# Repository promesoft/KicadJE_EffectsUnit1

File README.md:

# KicadJE_EffectsUnit1
JE-EU1 - PT2399 based reverb - distortion units
Eurorack form factor

# MK1 Design
## Status - operational
# Status - Secondary tests
## Initial 
| Stage  | Detail | Status |
| ------------- | ------------- | ------------- |
| create material  | sch/pcb | produced Rev A  |
| | gerber | Produced |
| production  | ordered  | YES |
|  | produced | YES |
|  | delivered | YES |
## Preliminary validation
| Test  | Detail | Status |
| ------------- | ------------- | ------------- |
| Initial Inspection |  | OK |
| Initial Technical Test | PT2399 | OK - See Errata |
| Initial Technical Test | Counter  | OK |
| Initial Technical Test | Bitcrunch |  |
| Initial Product Test | PT2399 | OK |
| Initial Product Test | Counter | OK |
| Initial Product Test | Bitcrunch  | OK - LFO w Distortion |
| Initial Power Consumption | PT2399 | 40-60mA ! +12v depending on VCO circuit |
| Initial Power Consumption | Counter | 20mA +12v  |
| Initial Power Consumption | Bitcrunch | +12v +5v -12v |
| Initial Power Consumption | LFO | +12v +5v -12v |

## Secondary validation
| Test  | Detail | Status |
| ------------- | ------------- |------------- |
| Product Test | PT2399 | ok after mod |
| Product Test | Counter | OK |
| Product Test | LFO Distortion | OK - dist too much |
| Product Test | Bitcrush Distortion |  |
| Quality | LFO | good - distortion is questionable effect |
| Quality | Bitcrush |  |
| Quality | Counter | Good - needs input prot |
| Quality | PT2399 | ongoing |
| Long Term Product Test | PT2399 | Modded version installed in rack |
| Long Term Product Test | Counter | installed in rack |
| Long Term Product Test | Bitcrush |  |
| Long Term Product Test | LFO | installed in rack |

## Software 
| Test  | Detail | Status |
| ------------- | ------------- |------------- |
| Initial SW | copy from MK1 and adjusted | OK! |
| Bitcrush | UI | |
| Bitcrush | Crush function | |
| LFO Control | UI | Individual speed and waveform impl |
| LFO Control | Function | Individual LFO implemented |
| LFO Control | Input | 3x Trigger done |

## Errata
### ERRATA - PT2399
 * 78L05 inv pinout
 * MMBT2222 wrong pinout - workaround flip and turn
 * Delay time pot reversed
 * PT2399 occational latchup with modification
 * SW101 and S105W are wired wrong to enable Dist on/off
### ERRATA - Counter
### ERRATA - Bitcrunch
 * SW 101 and SW105 should change footprint (too small for MT202)
 * D110 and D111 is 0805 and cannot be fitted with SOD123
## Issues and Notes
### Issues and Notes - PT2399
 * Replace 20k across Q203 w Yellow LED
 * Replace 120k R214 with 47k
 * Move C222 across RV202 - move D2015 across R214 and remove Q202+R213
 * Consider Vactrol of RV202 and RV201
 * Consider +5V supply...
### Issues and Notes - Counter
 * Replace 100uF C310 with 10-22uF (consider a switch for next rev)
 * Reset/Clk in Trigger not 5V tolerant
 * Add I/O protection

### Issues and Notes - Bit Crunch
LFO only values:
 * 11k = 10k
 * 22k = 10k
 * 33k = 10k
 * 44k = 10k
 * 11n = 100n
 * 22n = 100n
 * 33n = 100n
 * 44n = 100n
 * D118 - D117 remove
 * Optional D111 - D110
Dist/Bitcrush values has been added to the sch
 * Move LED D114 closer to Out9

### Workarounds

## Base Construction 
The idea is to have 3 different units.
Practically it may be required to fit the bitcrusher and the distortion in one unit.
### Distortion base board with Arduino Bitcrusher
 - 16pin Europower connector

### PT2399 base board 
 - 10pin Europower connector
 - BC547 or BC337 NPN and Zener 7v5 regulator followed by 78L05 regulator
 - PT2399 echo circuit with anti lockup circuit for pin 6
 - 
### Binary counter and clock
 - 10pin Europower connector
 - Build around a CD4017 counter chip (SOP-14)

## Vital Components
 - Arduino Nano
 - PT2399
 - CD4017
 - NE555
 - Mini Jacks (PJ-321) 
 - ALPS RV09 potentiometer
 - TL072 or similar dual op amp
 - Diode clipping (silicium signal diodes, LED, power, shottkey, germanium
 
### Mechanical

The construction is inspired from
-----------------------------------------------------
 - https://www.electronics-tutorials.ws/waveforms/555_oscillator.html (Counter clock)
 - https://www.electrosmash.com/pt2399-analysis (PT2399 Reverb)
 - http://sim.okawa-denshi.jp/en/OPttool.php (Filter calc for MFB filter)
 - http://sim.okawa-denshi.jp/en/OPseikiLowkeisan.htm (Filter calc for Sallen Key filter (Out9 and Out10))

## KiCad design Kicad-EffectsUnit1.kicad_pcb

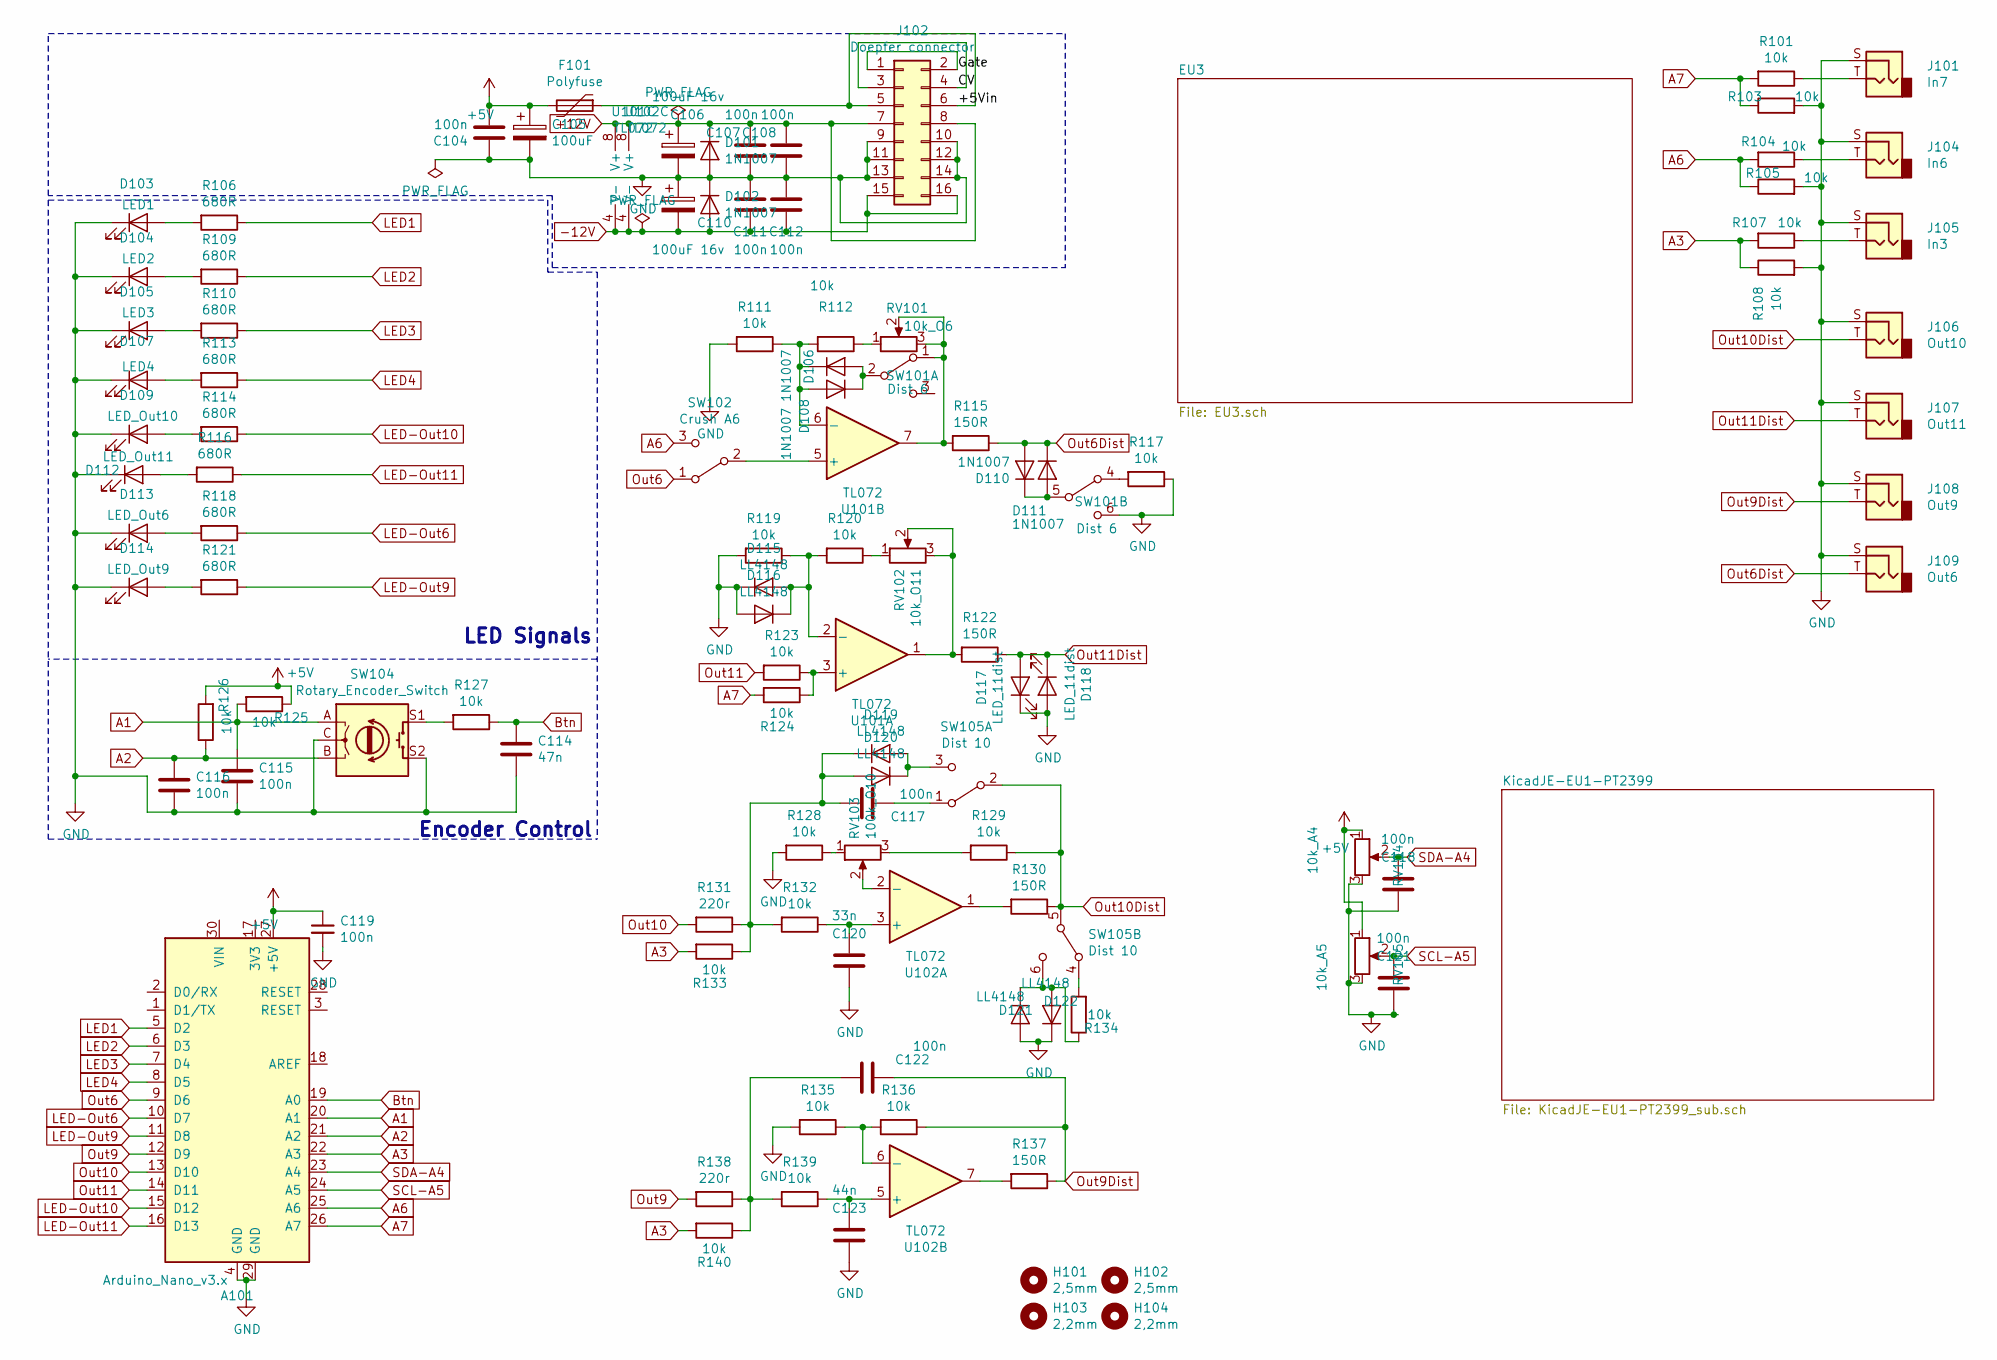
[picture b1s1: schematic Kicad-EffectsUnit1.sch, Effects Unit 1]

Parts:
A101: Arduino_Nano_v3.x; Arduino_Nano
C104, C107, C108, C111, C112, C115, C116, C117, C118, C119, C121, C122: 100n; C_0805_2012Metric_Pad1.15x1.40mm_HandSolder
C105: 100uF; CP_Radial_D5.0mm_P2.50mm
C106, C110: 100uF 16v; CP_Radial_D5.0mm_P2.50mm
C114: 47n; C_0805_2012Metric_Pad1.15x1.40mm_HandSolder
C120: 33n; C_0805_2012Metric_Pad1.15x1.40mm_HandSolder
C123: 44n; C_0805_2012Metric_Pad1.15x1.40mm_HandSolder
D101, D102, D106, D108: 1N1007; D_SOD-123
D103: LED1; LED_D3.0mm
D104: LED2; LED_D3.0mm
D105: LED3; LED_D3.0mm
D107: LED4; LED_D3.0mm
D109: LED_Out10; LED_D3.0mm
D110, D111: 1N1007; D_0805_2012Metric_Pad1.15x1.40mm_HandSolder
D112: LED_Out11; LED_D3.0mm
D113: LED_Out6; LED_D3.0mm
D114: LED_Out9; LED_D3.0mm
D115, D116, D119, D120, D121, D122: LL4148; D_MiniMELF
D117: LED_11dist; LED_0805_2012Metric_Pad1.15x1.40mm_HandSolder
D118: LED_11dist; D_0805_2012Metric_Pad1.15x1.40mm_HandSolder
F101: Polyfuse; Fuse_1206_3216Metric_Pad1.42x1.75mm_HandSolder
H101, H102: 2,5mm; MountingHole_2.5mm_Pad_Via
H103: 2,2mm; MountingHole_2.5mm_Pad_Via
H104: 2,2mm; MountingHole_2.2mm_M2_Pad_Via
J101: In7; PJ301SM
J102: Doepfer connector; PinSocket_2x08_P2.54mm_Vertical
J104: In6; PJ301SM
J105: In3; PJ301SM
J106: Out10; PJ301SM
J107: Out11; PJ301SM
J108: Out9; PJ301SM
J109: Out6; PJ301SM
R101, R103, R104, R105, R107, R108, R111, R112, R117, R119, R120, R123, R124, R125, R126, R127, R128, R129, R132, R133, R134, R135, R136, R139, R140: 10k; R_0805_2012Metric_Pad1.15x1.40mm_HandSolder
R106, R109, R110, R113, R114, R116, R118, R121: 680R; R_0805_2012Metric_Pad1.15x1.40mm_HandSolder
R115, R122, R130, R137: 150R; R_0805_2012Metric_Pad1.15x1.40mm_HandSolder
R131, R138: 220r; R_0805_2012Metric_Pad1.15x1.40mm_HandSolder
RV101: 10k_O6; Potentiometer_China_RK09_Single_Vertical_AJ
RV102: 10k_O11; Potentiometer_China_RK09_Single_Vertical_AJ
RV103: 100k_O10; Potentiometer_China_RK09_Single_Vertical_AJ
RV104: 10k_A4; Potentiometer_China_RK09_Single_Vertical_AJ
RV105: 10k_A5; Potentiometer_China_RK09_Single_Vertical_AJ
SW101: Dist 6; SPDTx2
SW102: Crush A6; SP1MS1
SW104: Rotary_Encoder_Switch; RotaryEncoder_Alps_EC11E-Switch_Vertical_H20mm
SW105: Dist 10; SPDTx2
U101, U102: TL072; AJ_SO-8_5.3x6.2mm_P1.27mm

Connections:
+5V: A101.27 (+5V), C104.2, C105.1, C119.1, F101.2, R125.1, R126.2, RV104.1, RV105.1
+12V: C106.1, C107.2, C108.2, D101.1 (K), J102.7, J102.8, U101.8 (V+), U102.8 (V+)
-12V: C110.2, C111.1, C112.1, D102.2 (A), J102.15, J102.16, U101.4 (V-), U102.4 (V-)
/+5Vin: F101.1, J102.5, J102.6
/CV: J102.3, J102.4
/Gate: J102.1, J102.2
A1: A101.20 (A1), C115.1, R125.2, SW104.A
A2: A101.21 (A2), C116.1, R126.1, SW104.B
A3: A101.22 (A3), R107.2, R108.1, R133.2, R140.2
A6: A101.25 (A6), R104.2, R105.1, SW102.3 (C)
A7: A101.26 (A7), R101.2, R103.1, R124.2
Btn: A101.19 (A0), C114.1, R127.1
GND: A101.4 (GND), A101.29 (GND), C104.1, C105.2, C106.2, C107.1, C108.1, C110.1, C111.2, C112.2, C114.2, C115.2, C116.2, C118.2, C119.2, C120.2, C121.2, C123.2, D101.2 (A), D102.1 (K), D103.1 (K), D104.1 (K), D105.1 (K), D107.1 (K), D109.1 (K), D112.1 (K), D113.1 (K), D114.1 (K), D115.1 (K), D116.2 (A), D117.1 (K), D118.2 (A), D121.2 (A), D122.1 (K), J101.S, J102.9, J102.10, J102.11, J102.12, J102.13, J102.14, J104.S, J105.S, J106.S, J107.S, J108.S, J109.S, R103.2, R105.2, R108.2, R111.2, R117.1, R119.2, R128.2, R135.2, RV104.3, RV105.3, SW101.6 (C), SW104.C, SW104.S2; also elsewhere on the board
LED1: A101.5 (D2), R106.1
LED2: A101.6 (D3), R109.1
LED3: A101.7 (D4), R110.1
LED4: A101.8 (D5), R113.1
LED-Out6: A101.10 (D7), R118.1
LED-Out9: A101.11 (D8), R121.1
LED-Out10: A101.15 (D12), R114.1
LED-Out11: A101.16 (D13), R116.1
unnamed: C117.1, SW105.1 (A)
unnamed: C117.2, D119.1 (K), D120.2 (A), R131.1, R132.2, R133.1
unnamed: C120.1, R132.1, U102.3 (+)
unnamed: C122.2, R138.1, R139.2, R140.1
unnamed: C123.1, R139.1, U102.5 (+)
unnamed: D103.2 (A), R106.2
unnamed: D104.2 (A), R109.2
unnamed: D105.2 (A), R110.2
unnamed: D106.1 (K), D108.2 (A), R111.1, R112.2, U101.6 (-)
unnamed: D106.2 (A), D108.1 (K), SW101.2 (B)
unnamed: D107.2 (A), R113.2
unnamed: D109.2 (A), R114.2
unnamed: D110.1 (K), D111.2 (A), SW101.5 (B)
unnamed: D112.2 (A), R116.2
unnamed: D113.2 (A), R118.2
unnamed: D114.2 (A), R121.2
unnamed: D115.2 (A), D116.1 (K), R119.1, R120.2, U101.2 (-)
unnamed: D119.2 (A), D120.1 (K), SW105.3 (C)
unnamed: D121.1 (K), D122.2 (A), R134.1, SW105.6 (C)
unnamed: J101.T, R101.1
unnamed: J104.T, R104.1
unnamed: J105.T, R107.1
unnamed: R112.1, RV101.1
unnamed: R115.2, RV101.2, RV101.3, SW101.1 (A), U101.7
unnamed: R117.2, SW101.4 (A)
unnamed: R120.1, RV102.1
unnamed: R122.2, RV102.2, RV102.3, U101.1
unnamed: R123.1, R124.1, U101.3 (+)
unnamed: R127.2, SW104.S1
unnamed: R128.1, RV103.1
unnamed: R129.2, RV103.3
unnamed: R130.2, U102.1
unnamed: R134.2, SW105.4 (A)
unnamed: R135.1, R136.2, U102.6 (-)
unnamed: R137.2, U102.7
unnamed: RV103.2, U102.2 (-)
unnamed: SW102.2 (B), U101.5 (+)
Out6: A101.9 (D6), SW102.1 (A); also elsewhere on the board
Out6Dist: D110.2 (A), D111.1 (K), J109.T, R115.1
Out9: A101.12 (D9), R138.2; also elsewhere on the board
Out9Dist: C122.1, J108.T, R136.1, R137.1
Out10: A101.13 (D10), R131.2
Out10Dist: J106.T, R129.1, R130.1, SW105.2 (B), SW105.5 (B)
Out11: A101.14 (D11), R123.2
Out11Dist: D117.2 (A), D118.1 (K), J107.T, R122.1
SCL-A5: A101.24 (A5), C121.1, RV105.2
SDA-A4: A101.23 (A4), C118.1, RV104.2

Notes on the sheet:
LED Signals
Encoder Control

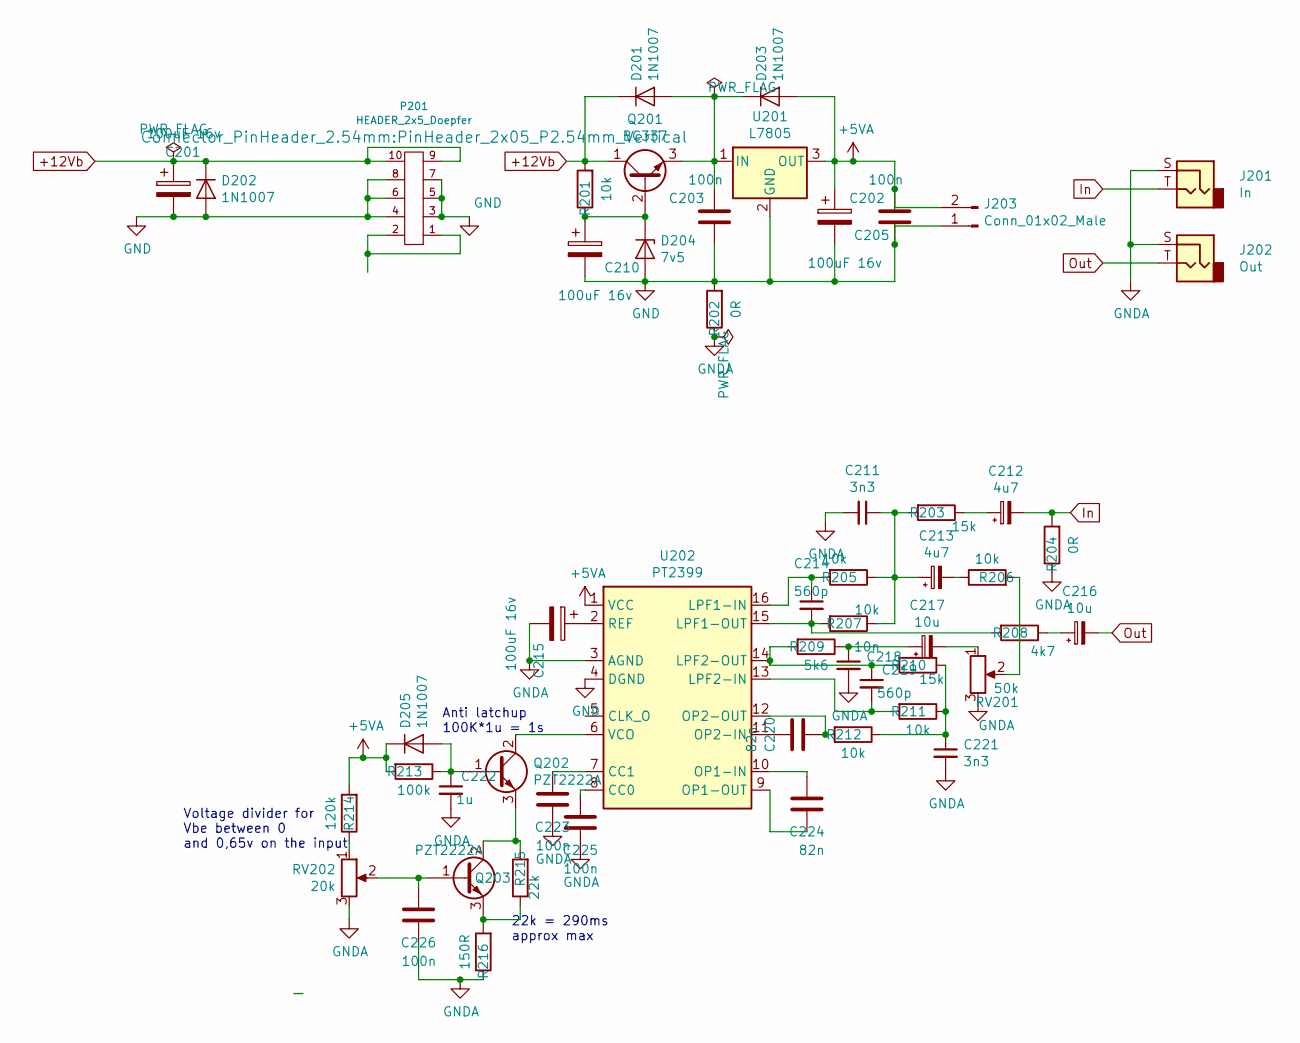
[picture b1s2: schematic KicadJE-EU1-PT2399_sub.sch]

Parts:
C201, C205, C210, C215: 100uF 16v; CP_Radial_D5.0mm_P2.50mm
C202, C203, C223, C225, C226: 100n; C_0805_2012Metric_Pad1.15x1.40mm_HandSolder
C211, C221: 3n3; C_0805_2012Metric_Pad1.15x1.40mm_HandSolder
C212, C213: 4u7; C_0805_2012Metric_Pad1.15x1.40mm_HandSolder
C214, C219: 560p; C_0805_2012Metric_Pad1.15x1.40mm_HandSolder
C216, C217: 10u; C_0805_2012Metric_Pad1.15x1.40mm_HandSolder
C218: 10n; C_0805_2012Metric_Pad1.15x1.40mm_HandSolder
C220, C224: 82n; C_0805_2012Metric_Pad1.15x1.40mm_HandSolder
C222: 1u; C_0805_2012Metric_Pad1.15x1.40mm_HandSolder
D201, D202, D203, D205: 1N1007; D_SOD-123
D204: 7v5; D_MiniMELF
J201: In; PJ301SM
J202: Out; PJ301SM
J203: Conn_01x02_Male; PinHeader_1x02_P2.54mm_Vertical
P201: HEADER_2x5_Doepfer; PinHeader_2x05_P2.54mm_Vertical
Q201: BC337; TO-92_Inline
Q202, Q203: PZT2222A; SOT-23
R201, R205, R206, R207, R211, R212: 10k; R_0805_2012Metric_Pad1.15x1.40mm_HandSolder
R202, R204: 0R; R_0805_2012Metric_Pad1.15x1.40mm_HandSolder
R203, R210: 15k; R_0805_2012Metric_Pad1.15x1.40mm_HandSolder
R208: 4k7; R_0805_2012Metric_Pad1.15x1.40mm_HandSolder
R209: 5k6; R_0805_2012Metric_Pad1.15x1.40mm_HandSolder
R213: 100k; R_0805_2012Metric_Pad1.15x1.40mm_HandSolder
R214: 120k; R_0805_2012Metric_Pad1.15x1.40mm_HandSolder
R215: 22k; R_0805_2012Metric_Pad1.15x1.40mm_HandSolder
R216: 150R; R_0805_2012Metric_Pad1.15x1.40mm_HandSolder
RV201: 50k; Potentiometer_China_RK09_Single_Vertical_AJ
RV202: 20k; Potentiometer_China_RK09_Single_Vertical_AJ
U201: L7805; TO-92
U202: PT2399; DIP-16_W7.62mm

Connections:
+5VA: C202.2, C205.1, D203.2 (A), D205.1 (K), J203.2, R213.2, R214.2, U201.3 (OUT), U202.1 (VCC)
+12Vb: C201.1, D201.1 (K), D202.1 (K), P201.9 (+12), P201.10 (+12), Q201.1 (C), R201.2
GND: C201.2, C202.1, C203.1, C205.2, C210.2, D202.2 (A), D204.2 (A), J203.1, P201.3 (GND), P201.4 (GND), P201.5 (GND), P201.6 (GND), P201.7 (GND), P201.8 (GND), R202.2, U201.2 (GND), U202.4 (DGND); also elsewhere on the board
GNDA: C211.2, C215.2, C218.2, C221.2, C222.2, C223.1, C225.1, C226.1, J201.S, J202.S, R202.1, R204.1, R216.1, RV201.3, RV202.3, U202.3 (AGND)
In: C212.2, J201.T, R204.2
unnamed: C203.2, D201.2 (A), D203.1 (K), Q201.3 (E), U201.1 (IN)
unnamed: C210.1, D204.1 (K), Q201.2 (B), R201.1
unnamed: C211.1, C213.1, R203.2, R205.1, R207.1
unnamed: C212.1, R203.1
unnamed: C213.2, R206.1
unnamed: C214.1, R205.2, U202.16 (LPF1-IN)
unnamed: C214.2, R207.2, R208.2, U202.15 (LPF1-OUT)
unnamed: C215.1, U202.2 (REF)
unnamed: C216.1, R208.1
unnamed: C217.1, C218.1, R209.1
unnamed: C217.2, RV201.1
unnamed: C219.1, R209.2, R210.2, U202.14 (LPF2-OUT)
unnamed: C219.2, R211.2, U202.13 (LPF2-IN)
unnamed: C220.1, U202.11 (OP2-IN)
unnamed: C220.2, R212.2, U202.12 (OP2-OUT)
unnamed: C221.1, R210.1, R211.1, R212.1
unnamed: C222.1, D205.2 (A), Q202.1 (B), R213.1
unnamed: C223.2, U202.7 (CC1)
unnamed: C224.1, U202.9 (OP1-OUT)
unnamed: C224.2, U202.10 (OP1-IN)
unnamed: C225.2, U202.8 (CC0)
unnamed: C226.2, Q203.1 (B), RV202.2
unnamed: P201.1 (-12), P201.2 (-12)
unnamed: Q202.2 (C), U202.6 (VCO)
unnamed: Q202.3 (E), Q203.2 (C), R215.2
unnamed: Q203.3 (E), R215.1, R216.2
unnamed: R206.2, RV201.2
unnamed: R214.1, RV202.1
Out: C216.2, J202.T

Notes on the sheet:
Voltage divider for Vbe between 0 and 0,65v on the input
Anti latchup 100K*1u = 1s
22k = 290ms approx max

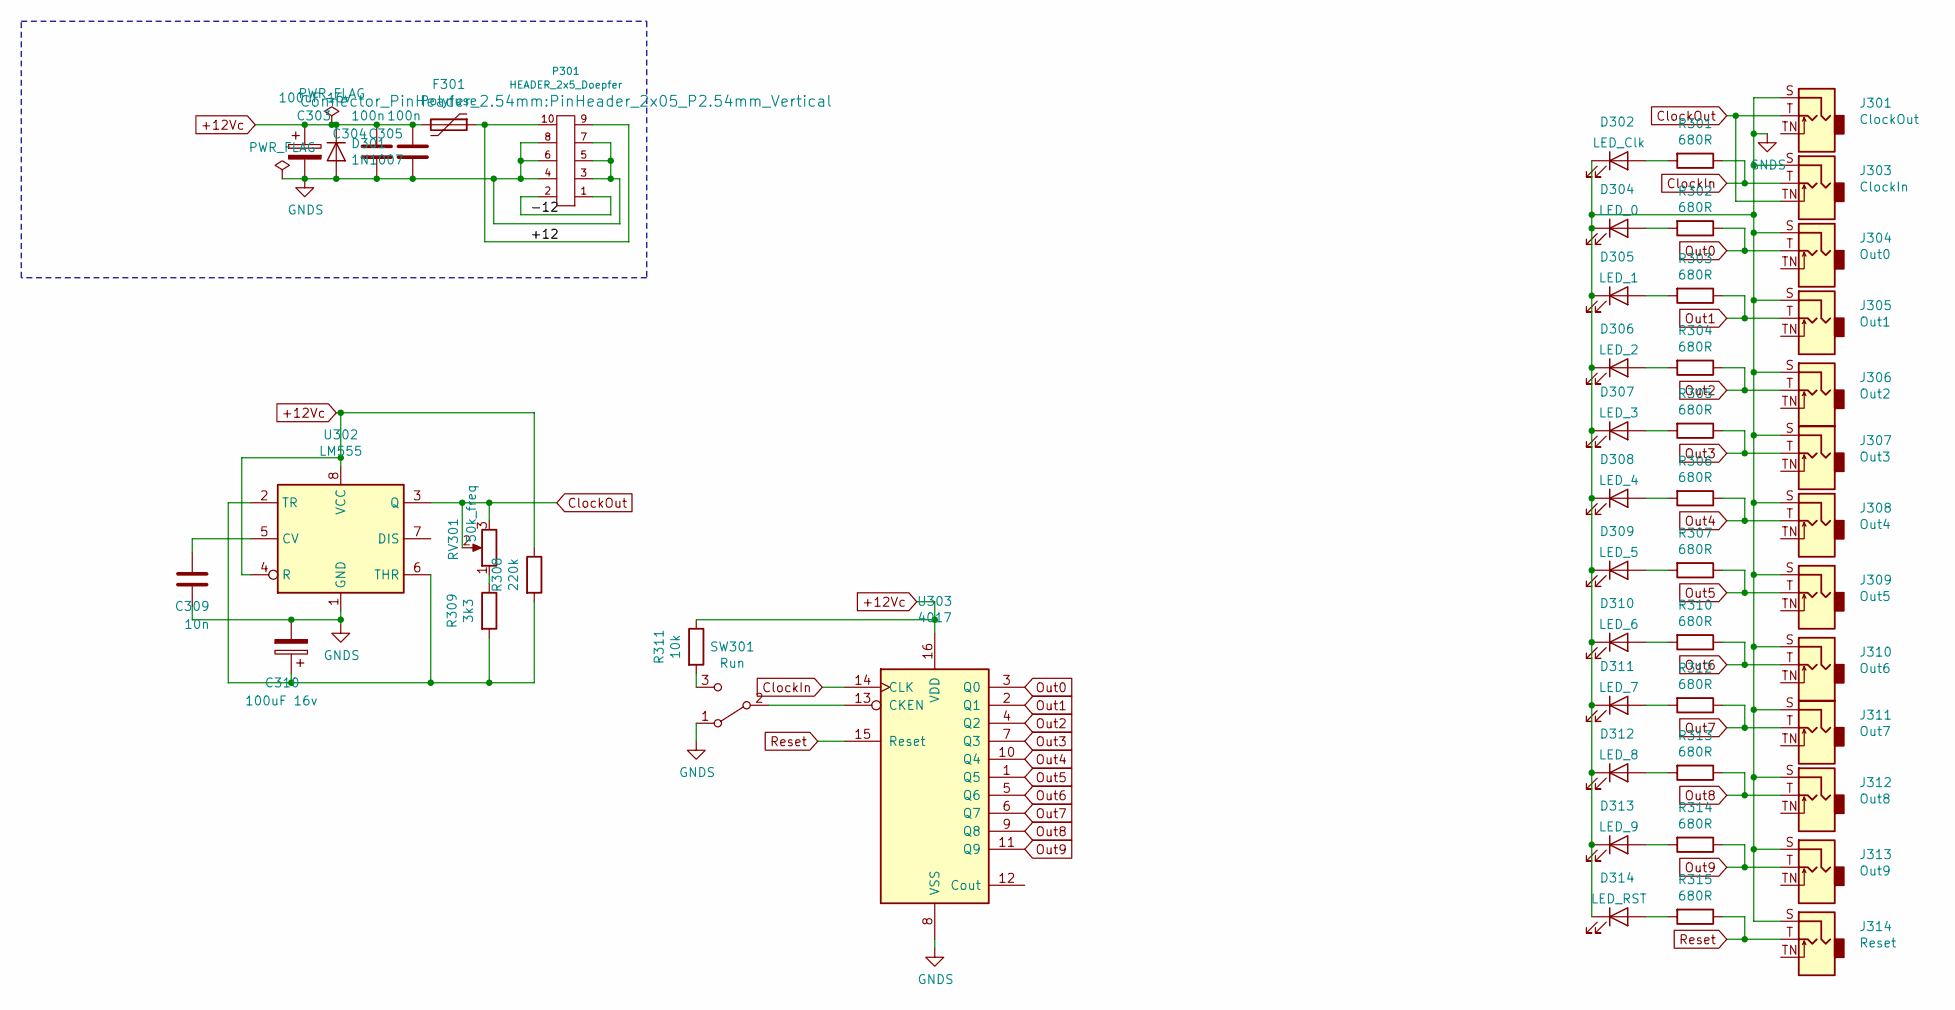
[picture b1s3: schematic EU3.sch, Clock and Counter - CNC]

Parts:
C303, C310: 100uF 16v; CP_Radial_D5.0mm_P2.50mm
C304, C305: 100n; C_0805_2012Metric_Pad1.15x1.40mm_HandSolder
C309: 10n; C_0805_2012Metric_Pad1.15x1.40mm_HandSolder
D301: 1N1007; D_SOD-123
D302: LED_Clk; LED_D3.0mm
D304: LED_0; LED_D3.0mm
D305: LED_1; LED_D3.0mm
D306: LED_2; LED_D3.0mm
D307: LED_3; LED_D3.0mm
D308: LED_4; LED_D3.0mm
D309: LED_5; LED_D3.0mm
D310: LED_6; LED_D3.0mm
D311: LED_7; LED_D3.0mm
D312: LED_8; LED_D3.0mm
D313: LED_9; LED_D3.0mm
D314: LED_RST; LED_D3.0mm
F301: Polyfuse; Fuse_1206_3216Metric_Pad1.42x1.75mm_HandSolder
J301: ClockOut; PJ301SM
J303: ClockIn; PJ301SM
J304: Out0; PJ301SM
J305: Out1; PJ301SM
J306: Out2; PJ301SM
J307: Out3; PJ301SM
J308: Out4; PJ301SM
J309: Out5; PJ301SM
J310: Out6; PJ301SM
J311: Out7; PJ301SM
J312: Out8; PJ301SM
J313: Out9; PJ301SM
J314: Reset; PJ301SM
P301: HEADER_2x5_Doepfer; PinHeader_2x05_P2.54mm_Vertical
R301, R302, R303, R304, R305, R306, R307, R310, R312, R313, R314, R315: 680R; R_0805_2012Metric_Pad1.15x1.40mm_HandSolder
R308: 220k; R_0805_2012Metric_Pad1.15x1.40mm_HandSolder
R309: 3k3; R_0805_2012Metric_Pad1.15x1.40mm_HandSolder
R311: 10k; R_0805_2012Metric_Pad1.15x1.40mm_HandSolder
RV301: 50k_freq; Potentiometer_China_RK09_Single_Vertical_AJ
SW301: Run; SP1MS1
U302: LM555; AJ_SO-8_5.3x6.2mm_P1.27mm
U303: 4017; SOIC-16_4.55x10.3mm_P1.27mm

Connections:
+12Vc: C303.1, C304.2, C305.2, D301.1 (K), F301.2, R308.1, R311.1, U302.4 (R), U302.8 (VCC), U303.16 (VDD)
ClockIn: J303.T, R301.1, U303.14 (CLK)
ClockOut: J301.T, J303.TN, RV301.2, RV301.3, U302.3 (Q)
GNDS: C303.2, C304.1, C305.1, C309.1, C310.2, D301.2 (A), D302.1 (K), D304.1 (K), D305.1 (K), D306.1 (K), D307.1 (K), D308.1 (K), D309.1 (K), D310.1 (K), D311.1 (K), D312.1 (K), D313.1 (K), D314.1 (K), J301.S, J303.S, J304.S, J305.S, J306.S, J307.S, J308.S, J309.S, J310.S, J311.S, J312.S, J313.S, J314.S, P301.3 (GND), P301.4 (GND), P301.5 (GND), P301.6 (GND), P301.7 (GND), P301.8 (GND), SW301.1 (A), U302.1 (GND), U303.8 (VSS)
unnamed: C309.2, U302.5 (CV)
unnamed: C310.1, R308.2, R309.2, U302.2 (TR), U302.6 (THR)
unnamed: D302.2 (A), R301.2
unnamed: D304.2 (A), R302.2
unnamed: D305.2 (A), R303.2
unnamed: D306.2 (A), R304.2
unnamed: D307.2 (A), R305.2
unnamed: D308.2 (A), R306.2
unnamed: D309.2 (A), R307.2
unnamed: D310.2 (A), R310.2
unnamed: D311.2 (A), R312.2
unnamed: D312.2 (A), R313.2
unnamed: D313.2 (A), R314.2
unnamed: D314.2 (A), R315.2
unnamed: F301.1, P301.9 (+12), P301.10 (+12)
unnamed: P301.1 (-12), P301.2 (-12)
unnamed: R309.1, RV301.1
unnamed: R311.2, SW301.3 (C)
unnamed: SW301.2 (B), U303.13 (CKEN)
Out0: J304.T, R302.1, U303.3 (Q0)
Out1: J305.T, R303.1, U303.2 (Q1)
Out2: J306.T, R304.1, U303.4 (Q2)
Out3: J307.T, R305.1, U303.7 (Q3)
Out4: J308.T, R306.1, U303.10 (Q4)
Out5: J309.T, R307.1, U303.1 (Q5)
Out6: J310.T, R310.1, U303.5 (Q6); also elsewhere on the board
Out7: J311.T, R312.1, U303.6 (Q7)
Out8: J312.T, R313.1, U303.9 (Q8)
Out9: J313.T, R314.1, U303.11 (Q9); also elsewhere on the board
Reset: J314.T, R315.1, U303.15 (Reset)

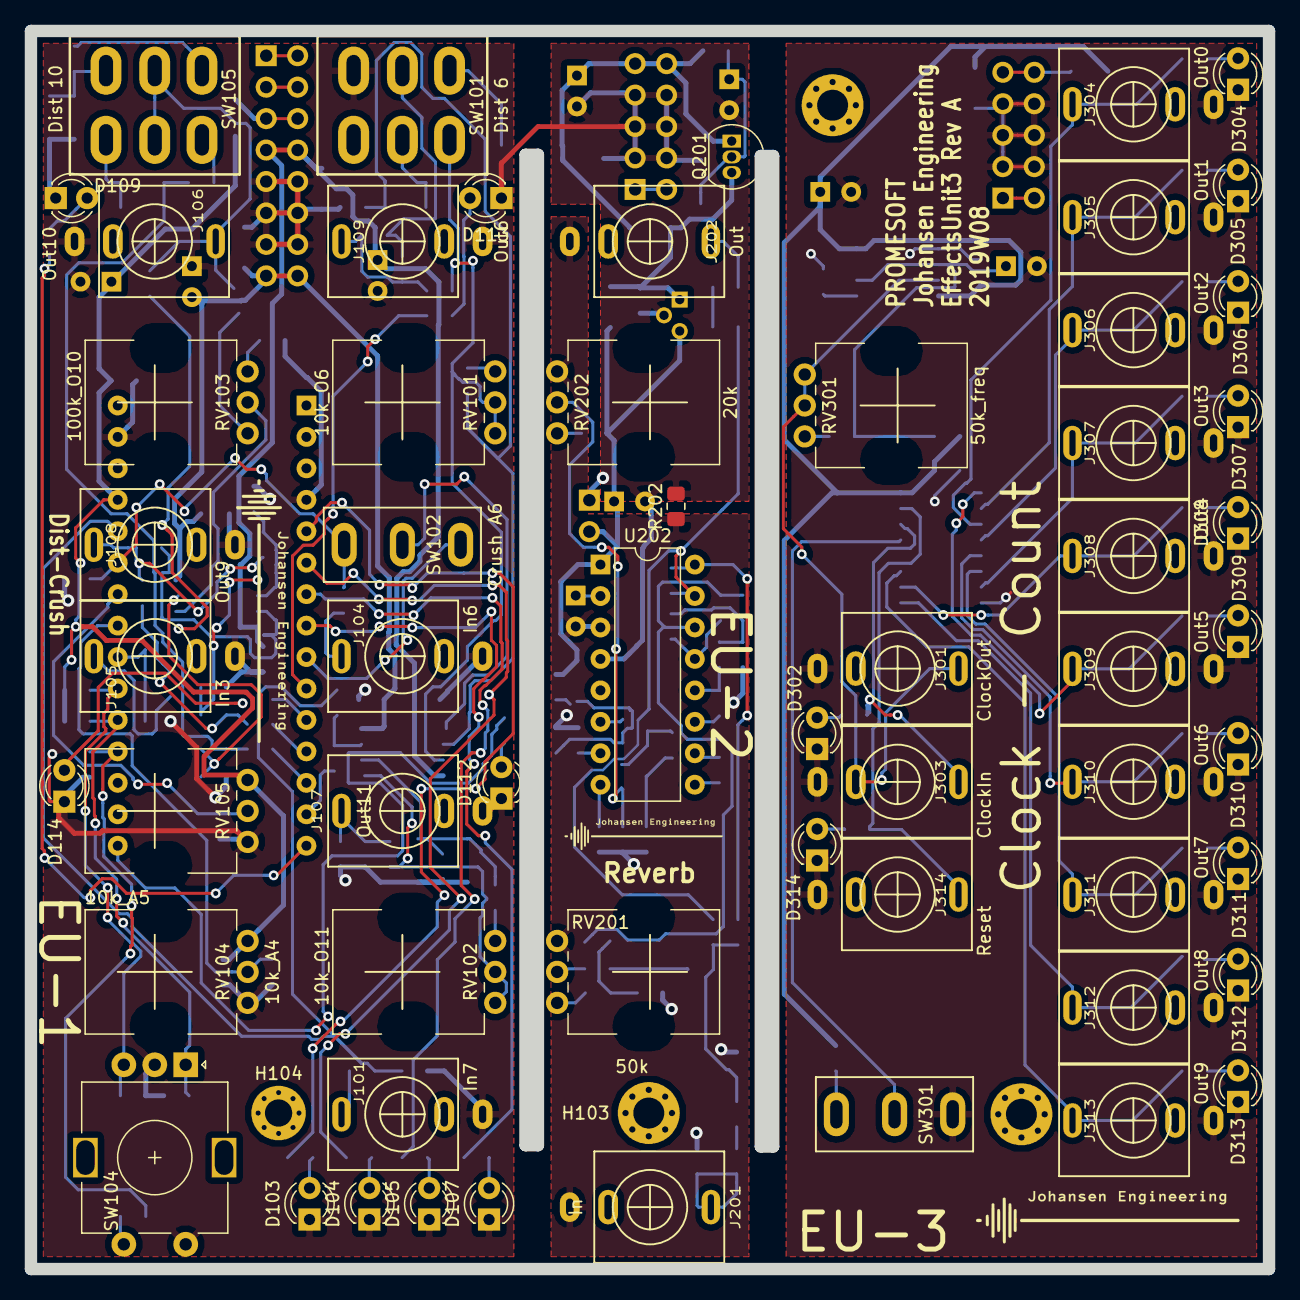
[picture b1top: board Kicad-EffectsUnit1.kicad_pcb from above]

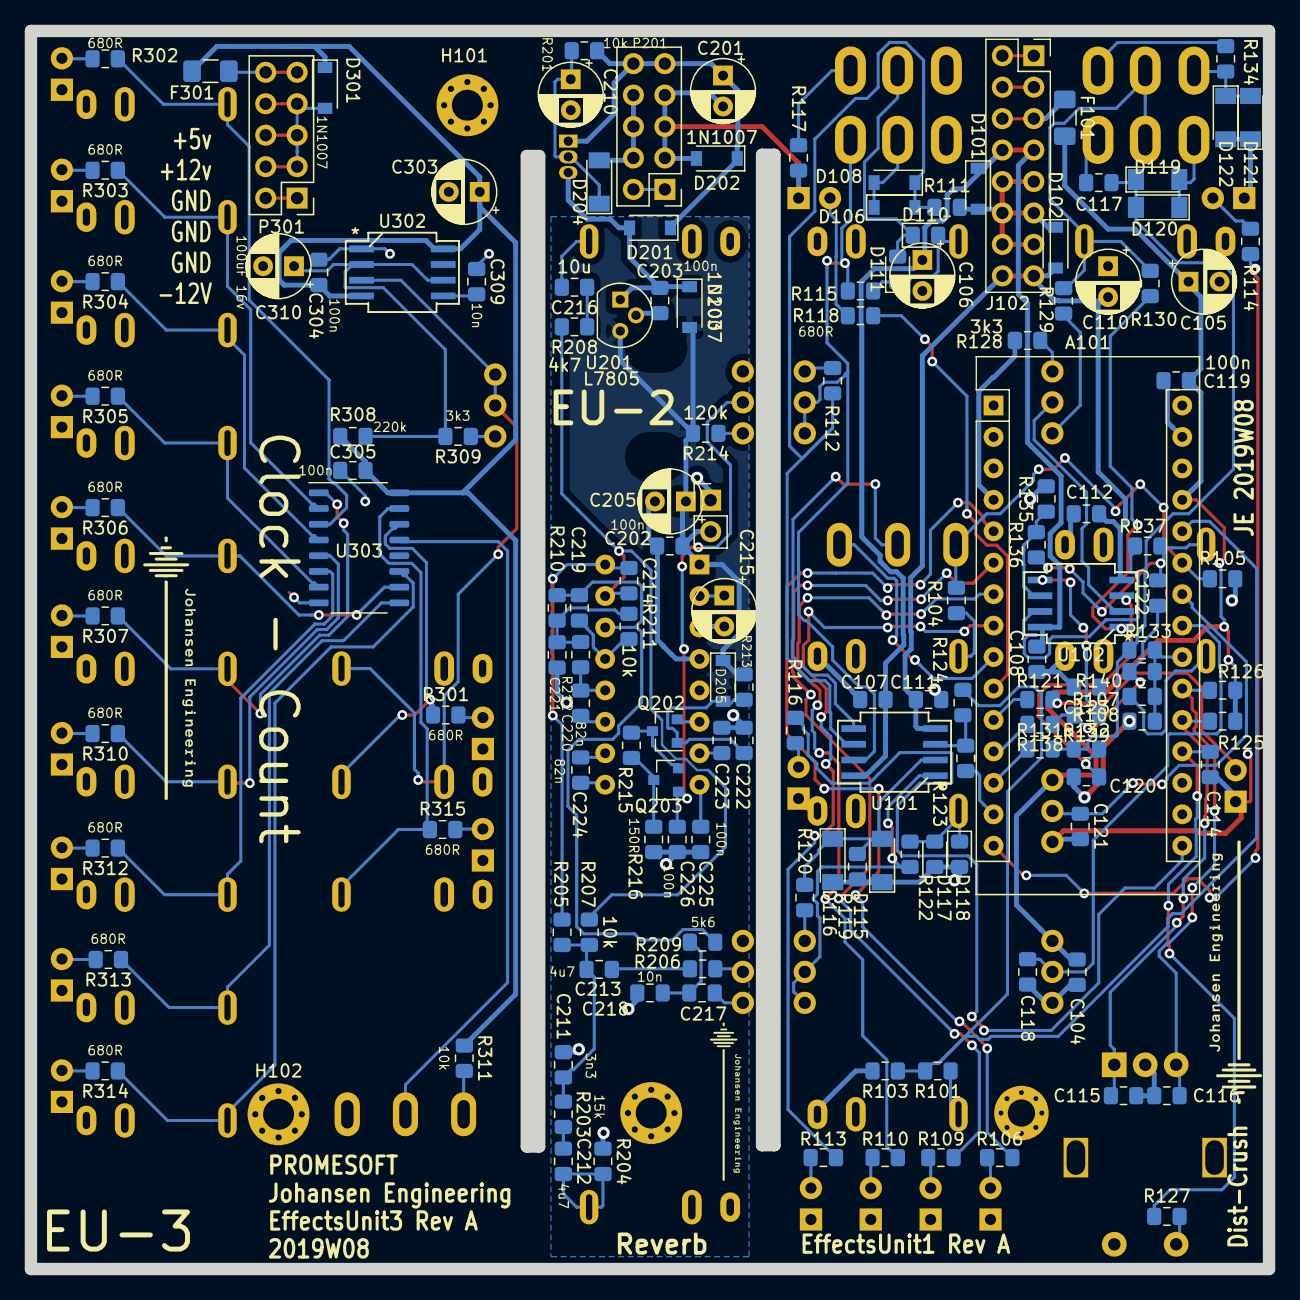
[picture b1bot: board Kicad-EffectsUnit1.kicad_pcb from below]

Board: 2 copper layers, 100.0 x 100.0 mm, 209 parts (149 on the bottom side), 133 nets.

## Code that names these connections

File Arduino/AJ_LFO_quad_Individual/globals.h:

#include <EEPROM.h>
/* -----------------------------------------------
 *  GLOBAL DEFINES
 * -----------------------------------------------
 */
//OVERRIDE PINS FOR LFO
#define LFO0 6 // Sets Pin PWM1 = Out 6 (top right)
#define LFO1 11 // Sets Pin PWM2 = Out 11 (mid right)
#define LFO2 10 // Sets Pin PWM6 = Out 10 (top left)
#define LFO3 9 // Sets Pin PWM4 = Out 9 (mid left)

#define SWpin A0 //add 100nF to GND for debounce 
#define Apin A1 //add 100nF to GND for debounce
#define Bpin A2 //add 100nF to GND for debounce

#define LeftIn A3 // Lowest Left feeds to left two top outputs
#define LeftBottomPot A4 // Addon board
#define LeftTopPot A5 // Addon board
#define RightCenterIn A6 // Feeds to Right Top out
#define RightBottomIn A7 // Feeds to Right Center out

#define LED1 2
#define LED2 3
#define LED3 4
#define LED4 5
#define LED_Out6 7
#define LED_Out9 13
#define LED_Out10 12
#define LED_Out11 8

/* -----------------------------------------------
 *  GLOBAL VAR
 * -----------------------------------------------
 */
boolean A_old=0, B_old=1, SW_old=0;
boolean left = false, right = false, button = false;

boolean LEDSelData = false, LEDSel2Data = false; 
unsigned int encoder[4], buttoncnt = 0;
unsigned int state = 0; 
//For LFO - State 00 = Out6 - 01 = Out9 - 10 = Out10 - 11 = Out11
byte LFO_CH[4]; //(see state above)
boolean LEDData[4][4]; //(see state)

unsigned long lastwaveupdate = 0; // LFO millis timer between samples
unsigned int delayTime = 4; 
uint8_t tableStep = 0;
uint8_t PWMdata = 0;

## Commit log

2019-02-05 Initial sch
2019-02-05 Sch added switches and clipping diodes - init pcb
2019-02-05 Initial PCB and png
2019-02-06 PT2399 started
2019-02-06 PT2399 reference design impl in sch
2019-02-06 anti latchup initiated
    inspiration:
    https://www.electrosmash.com/images/tech/pt2399/PT2399_Transistor_Current_Sink_Pin6.png
2019-02-06 Basic circuit done
2019-02-06 more footprints
2019-02-09 footprint juggling
2019-02-09 Footprints
2019-02-11 Pin juggling on bit crusher
2019-02-24 PCB work
2019-02-24 sch pinout
2019-02-24 3D + PCB
2019-02-24 Removed components from PSU
2019-02-24 misc
2019-02-24 PREPARE for major restruct
2019-02-24 Reorganize #1
2019-02-24 Distortion - Bitcrunch components placed
2019-02-24 Before gnd flooding
2019-02-25 DRC done for Cruncher/Distortion
2019-02-25 Remove extra components from PT2399 and add EU3 diagram
2019-02-25 GNDS and GNDA
2019-02-25 argh Kicad not stable
2019-02-25 Components placed on PT2399
2019-02-25 Added 78L05 reg
2019-02-25 Counter and Clock added to EU-3
2019-02-26 change jacks
2019-02-26 SO8 SO16
2019-02-26 -12Vc and Opamp removed on Clock sch
2019-02-26 Large components placed EU3
2019-02-26 Replace 16pin doepfer with 10pin on EU3
2019-02-26 EU3 placed and routed
2019-02-26 Labels
2019-02-26 Labels and logos done
2019-02-27 Gerber
2019-02-28 3D and replaced som top silk text
2019-03-24 Create fp-info-cache
2019-03-26 pictures of PT2399
2019-03-31 filters
2019-03-31 filters 2
2019-04-01 Arduino LFO initiated
2019-04-01 Compiling
2019-04-01 LFO with distortion tested nicely!
2019-04-02 LFO Working with A4 and A5 as time/speed control
2019-04-02 Arduino - trigger ino
2019-04-02 Arduino - trigger - LFO 2D config array
2019-04-02 Arduino - LFO's broken
2019-04-02 Arduino - LFO w individual waveform and individual timebase working.
2019-04-03 LED output delayed 10000ms - A4 A5 controls delayed 1000ms - LFO sync LED delayed 5000ms
2019-04-17 Store pot values for step and speed
2019-04-17 Update AJ_LFO_quad_trigger.ino
    Stored values used in LFO when booting
2019-04-24 Save EEPROM writes
2019-04-24 Initial trigger function
2019-04-24 Retrigger state
2019-04-24 Trigger fixes
2019-04-25 Rev B initiated
2019-04-25 Counter with input protection and new stop/carry feature
2019-04-25 Switch 1/2 rev
2019-05-14 Bitcrusher initiated
2019-05-15 Initial 2x2channel Bitcrusher
    Left / Right division
    Lower right input only analogue dist
2019-05-15 1 in x 4 out
    Left bottom input - enabling analogue dual channel distortion on the right
2019-09-29 Rev 1,2 Counter Resistor on LED
